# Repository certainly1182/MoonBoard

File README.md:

# MoonBoard - 75% ISO Keyboard with Hall Effect Sensors
This repository contains the hardware for a 75% ISO keyboard powered by hall effect sensors.<br />
[Click here for the firmware repository!](https://github.com/RephlexZero/qmk_firmware/tree/adc_testing)

## Features
- Hall Effect Sensors for configurable trigger point & "rapid trigger" functionality.
- Per-key RGB Lighting.
- USB connection uses [Unified Daughterboard](https://unified-daughterboard.github.io/).
- STM32 Microcontroller.
- Buzzer.
- 128x32 OLED Display.
- Rotary Encoder.
- Powered by QMK Firmware.

## Images

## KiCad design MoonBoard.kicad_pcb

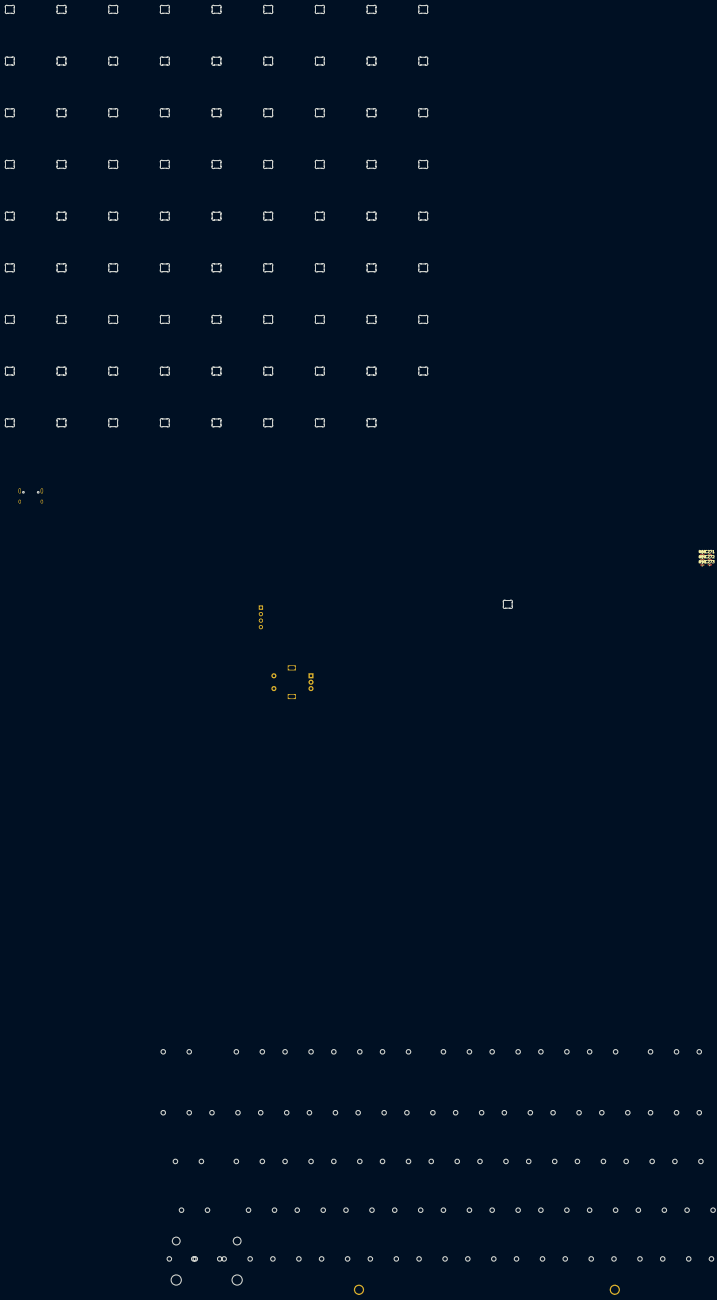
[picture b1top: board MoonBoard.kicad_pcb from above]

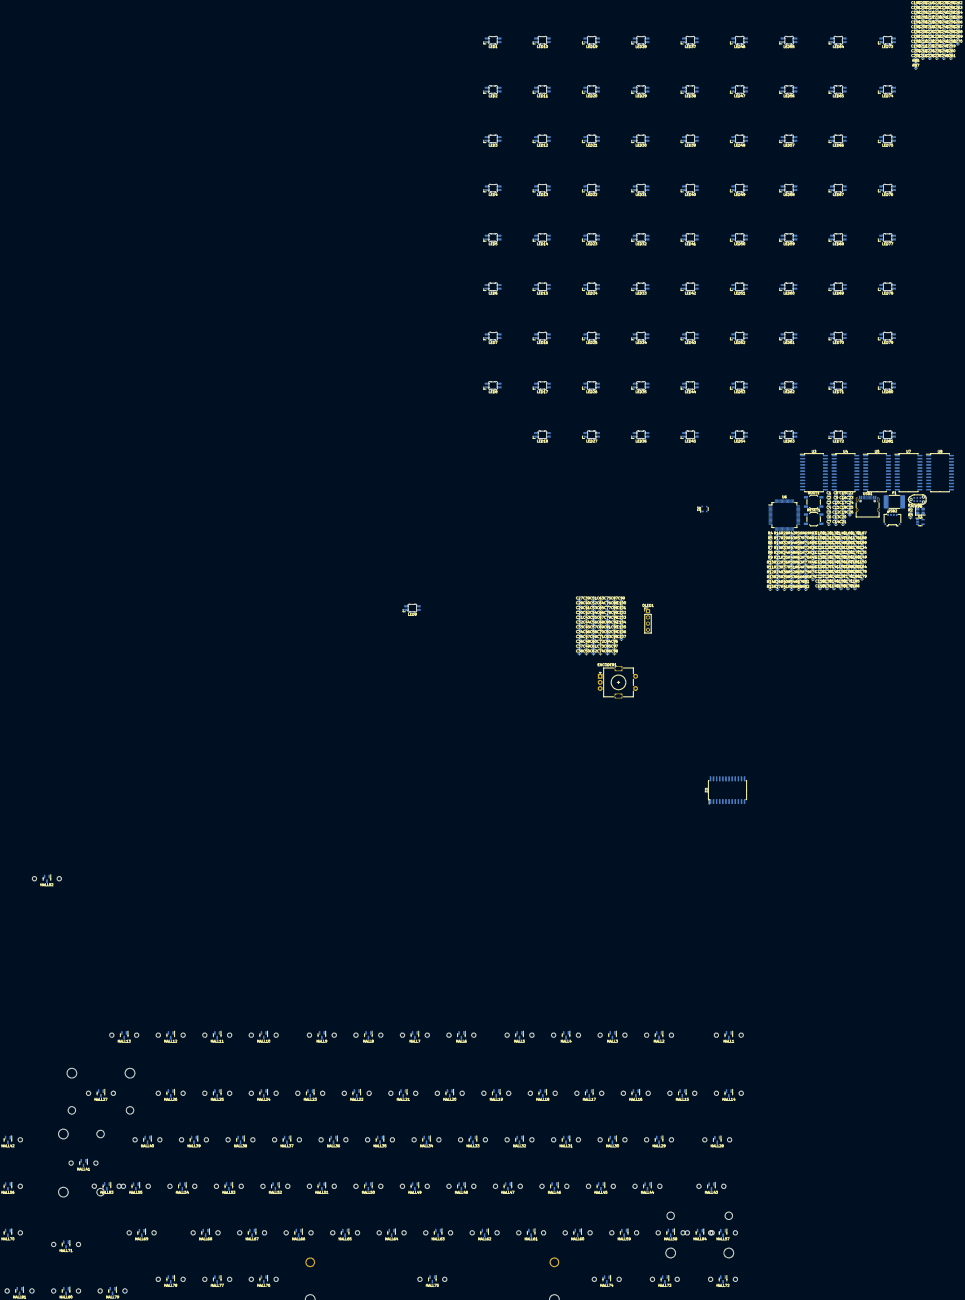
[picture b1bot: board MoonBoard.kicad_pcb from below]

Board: 2 copper layers, 551 parts (540 on the bottom side), 282 nets, no tracks yet.

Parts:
BOOT1: SW_SPST; SW_SPST_TL3342
C1, C2, C3, C4, C5, C6, C7, C12, C15, C16, C17, C18, C19, C20, C21, C22, C23, C24, C25, C26, C27, C28, C29, C30, C31, C32, C33, C34, C35, C36, C37, C38, C39, C40, C41, C42, C43, C44, C45, C46, C47, C48, C49, C50, C51, C52, C53, C54, C55, C56, C57, C58, C59, C60, C61, C62, C63, C64, C65, C66, C67, C68, C69, C70, C71, C72, C73, C74, C75, C76, C77, C78, C79, C80, C81, C82, C83, C84, C85, C86, C87, C88, C89, C90, C91, C92, C93, C94, C95, C96, C97, C98, C99, C100, C101, C102, C103, C104, C105, C106, C107, C108, C109, C110, C111, C112, C113, C114, C115, C116, C117, C118, C119, C120, C121, C122, C123, C124, C125, C126, C127, C128, C129, C130, C131, C132, C133, C134, C135, C136, C137, C138, C139, C140, C141, C142, C143, C144, C145, C146, C147, C148, C149, C150, C151, C152, C153, C154, C155, C156, C157, C158, C159, C160, C161, C162, C163, C164, C165, C166, C167, C168, C169, C170, C171, C172, C173, C174, C175, C176, C177, C178, C179, C180, C181, C182, C183, C184, C185, C186, C187, C188, C189, C190, C191, C192, C193, C194, C195, C196, C197, C198, C199, C200, C201, C202, C203, C204, C205, C206, C207, C208, C209, C210, C211, C212, C213, C214, C215, C216, C217, C218, C219, C220, C221, C222, C223, C224, C225, C226, C227, C228, C229, C230, C231, C232, C233, C234, C235, C236, C237, C238, C239, C240, C241, C242, C243, C244, C245, C246, C247, C248, C249, C250, C251, C252, C253, C254, C255, C256, C257, C258, C259, C260, C261, C262, C263, C264, C265, C266, C267, C268, C269, C270, C271, C272, C273: 100n; C_0402_1005Metric
C8, C9: 14p; C_0402_1005Metric
C10, C11: 2u2; C_0402_1005Metric
C13: 1u; C_0402_1005Metric
C14: 4u7; C_0402_1005Metric
D1: PRTR5V0U2X; SOT-143
ENCODER1: RotaryEncoder_Switch; RotaryEncoder_Alps_EC11E-Switch_Vertical_H20mm
F1: Fuse; Fuse_2920_7451Metric
HALL1, HALL2, HALL3, HALL4, HALL5, HALL6, HALL7, HALL8, HALL9, HALL10, HALL11, HALL12, HALL13, HALL14, HALL15, HALL16, HALL17, HALL18, HALL19, HALL20, HALL21, HALL22, HALL23, HALL24, HALL25, HALL26, HALL27, HALL29, HALL30, HALL31, HALL32, HALL33, HALL34, HALL35, HALL36, HALL37, HALL38, HALL39, HALL40, HALL41, HALL42, HALL44, HALL45, HALL46, HALL47, HALL48, HALL49, HALL50, HALL51, HALL52, HALL53, HALL54, HALL55, HALL56, HALL58, HALL59, HALL60, HALL61, HALL62, HALL63, HALL64, HALL65, HALL66, HALL67, HALL68, HALL70, HALL71, HALL75, HALL76, HALL77, HALL78, HALL79, HALL80, HALL81: SLSS49E-3; SLSS49E-3 with MX holes
HALL28, HALL82: SLSS49E-3; SLSS49E-3 with 1.5u MX holes
HALL43, HALL69: SLSS49E-3; SLSS49E-3 with 1.75u MX holes
HALL57, HALL72, HALL73, HALL74: SLSS49E-3; SLSS49E-3 with 1.25u MX holes
HALL83, HALL84: SLSS49E-3; SLSS49E-3 with 2.25 MX holes
LED1, LED2, LED3, LED4, LED5, LED6, LED7, LED8, LED9, LED10, LED11, LED12, LED13, LED14, LED15, LED16, LED17, LED18, LED19, LED20, LED21, LED22, LED23, LED24, LED25, LED26, LED27, LED28, LED29, LED30, LED31, LED32, LED33, LED34, LED35, LED36, LED37, LED38, LED39, LED40, LED41, LED42, LED43, LED44, LED45, LED46, LED47, LED48, LED49, LED50, LED51, LED52, LED53, LED54, LED55, LED56, LED57, LED58, LED59, LED60, LED61, LED62, LED63, LED64, LED65, LED66, LED67, LED68, LED69, LED70, LED71, LED72, LED73, LED74, LED75, LED76, LED77, LED78, LED79, LED80, LED81: MX_SK6812MINI-E; LED_MX_6028R
OLED1: Conn_01x04_Socket; PinHeader_1x04_P2.54mm_Vertical
R1, R2: 5k1; R_0402_1005Metric
R3, R4, R5, R6, R7, R8, R9, R10, R11, R12, R13, R14, R15, R16, R17, R18, R19, R20, R21, R22, R23, R24, R25, R26, R27, R28, R29, R30, R31, R32, R33, R34, R35, R36, R37, R38, R39, R40, R41, R42, R43, R44, R45, R46, R47, R48, R49, R50, R51, R52, R53, R54, R55, R56, R57, R58, R59, R60, R61, R62, R63, R64, R65, R66, R67, R68, R69, R70, R71, R72, R73, R74, R75, R76, R77, R78, R79, R80, R81, R82, R83, R84, R85, R88, R89, R90: 10k; R_0402_1005Metric
R86, R87: 470; R_0402_1005Metric
RESET1: SW_SPST; SW_SPST_TL3342
S27: STAB_MX_2u
S41: STAB_MX_ISO
S75: STAB_MX_P_6.25U; STAB_MX_P_6.25u
S83, S84: MX_stab; STAB_MX_2.25u
SWD1: TC2030_SWD; CON_TC2030_outlined
U1: AP2112K-3.3; SOT-23-5
U2, U3, U4, U5, U7, U8: CD74HC4067M; SOIC-24W_7.5x15.4mm_P1.27mm
U6: STM32F446RETx; LQFP-64_10x10mm_P0.5mm
USB1: USB_C_Receptacle_USB2.0; USB_C_Receptacle_HRO_TYPE-C-31-M-12
USB2: Conn_01x04_Socket; Molex_Pico-EZmate_78171-0004_1x04-1MP_P1.20mm_Vertical
Y1: 25MHz; Crystal_SMD_3225-4Pin_3.2x2.5mm

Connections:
+3V3: BOOT1.2 (B), C12.1, C13.1, C14.1, C15.1, C16.1, C17.1, C18.1, C19.1, C20.1, C21.1, C22.1, C23.1, C24.1, C25.1, C26.1, C27.1, C28.1, C29.1, C30.1, C31.1, C32.1, C33.1, C34.1, C35.1, C36.1, C37.1, C38.1, C39.1, C40.1, C41.1, C42.1, C43.1, C44.1, C45.1, C46.1, C47.1, C48.1, C49.1, C50.1, C51.1, C52.1, C53.1, C54.1, C55.1, C56.1, C57.1, C58.1, C59.1, C60.1, C61.1, C62.1, C63.1, C64.1, C65.1, C66.1, C67.1, C68.1, C69.1, C70.1, C71.1, C72.1, C73.1, C74.1, C75.1, C76.1, C77.1, C78.1, C79.1, C80.1, C81.1, C82.1, C83.1, C84.1, C85.1, C86.1, C87.1, C88.1, C89.1, C90.1, C91.1, C92.1, C93.1, C94.1, C95.1, C96.1, C97.1, C98.1, C99.1, C100.1, C101.1, C102.1, C103.1, C104.1, C105.1, C106.1, C107.1, ENCODER1.S1, HALL1.1 (VDD), HALL2.1 (VDD), HALL3.1 (VDD), HALL4.1 (VDD), HALL5.1 (VDD), HALL6.1 (VDD), HALL7.1 (VDD), HALL8.1 (VDD), HALL9.1 (VDD), HALL10.1 (VDD), HALL11.1 (VDD), HALL12.1 (VDD), HALL13.1 (VDD), HALL14.1 (VDD), HALL15.1 (VDD), HALL16.1 (VDD), HALL17.1 (VDD), HALL18.1 (VDD), HALL19.1 (VDD), HALL20.1 (VDD), HALL21.1 (VDD), HALL22.1 (VDD), HALL23.1 (VDD), HALL24.1 (VDD), HALL25.1 (VDD), HALL26.1 (VDD), HALL27.1 (VDD), HALL28.1 (VDD), HALL29.1 (VDD), HALL30.1 (VDD), HALL31.1 (VDD), HALL32.1 (VDD), HALL33.1 (VDD), HALL34.1 (VDD), HALL35.1 (VDD), HALL36.1 (VDD), HALL37.1 (VDD), HALL38.1 (VDD), HALL39.1 (VDD), HALL40.1 (VDD), HALL41.1 (VDD), HALL42.1 (VDD), HALL43.1 (VDD), HALL44.1 (VDD), HALL45.1 (VDD), HALL46.1 (VDD), HALL47.1 (VDD), HALL48.1 (VDD), HALL49.1 (VDD), HALL50.1 (VDD), HALL51.1 (VDD), HALL52.1 (VDD), HALL53.1 (VDD), HALL54.1 (VDD), HALL55.1 (VDD), HALL56.1 (VDD), HALL57.1 (VDD), HALL58.1 (VDD), HALL59.1 (VDD), HALL60.1 (VDD), HALL61.1 (VDD), HALL62.1 (VDD), HALL63.1 (VDD), HALL64.1 (VDD), HALL65.1 (VDD), HALL66.1 (VDD), HALL67.1 (VDD), HALL68.1 (VDD), HALL69.1 (VDD), HALL70.1 (VDD), HALL71.1 (VDD), HALL72.1 (VDD), HALL73.1 (VDD), HALL74.1 (VDD), HALL75.1 (VDD), HALL76.1 (VDD), HALL77.1 (VDD), HALL78.1 (VDD), HALL79.1 (VDD), HALL80.1 (VDD), HALL81.1 (VDD), HALL82.1 (VDD), HALL83.1 (VDD), HALL84.1 (VDD), SWD1.1 (VCC), U1.5 (VOUT), U6.1 (VBAT), U6.13 (VDDA), U6.19 (VDD), U6.32 (VDD), U6.48 (VDD), U6.64 (VDD)
+5V: C1.1, C2.1, C3.1, C4.1, C5.1, C6.1, C190.1, C191.1, C192.1, C193.1, C194.1, C195.1, C196.1, C197.1, C198.1, C199.1, C200.1, C201.1, C202.1, C203.1, C204.1, C205.1, C206.1, C207.1, C208.1, C209.1, C210.1, C211.1, C212.1, C213.1, C214.1, C215.1, C216.1, C217.1, C218.1, C219.1, C220.1, C221.1, C222.1, C223.1, C224.1, C225.1, C226.1, C227.1, C228.1, C229.1, C230.1, C231.1, C232.1, C233.1, C234.1, C235.1, C236.1, C237.1, C238.1, C239.1, C240.1, C241.1, C242.1, C243.1, C244.1, C245.1, C246.1, C247.1, C248.1, C249.1, C250.1, C251.1, C252.1, C253.1, C254.1, C255.1, C256.1, C257.1, C258.1, C259.1, C260.1, C261.1, C262.1, C263.1, C264.1, C265.1, C266.1, C267.1, C268.1, C269.1, C270.1, F1.2, LED1.1 (VDD), LED2.1 (VDD), LED3.1 (VDD), LED4.1 (VDD), LED5.1 (VDD), LED6.1 (VDD), LED7.1 (VDD), LED8.1 (VDD), LED9.1 (VDD), LED10.1 (VDD), LED11.1 (VDD), LED12.1 (VDD), LED13.1 (VDD), LED14.1 (VDD), LED15.1 (VDD), LED16.1 (VDD), LED17.1 (VDD), LED18.1 (VDD), LED19.1 (VDD), LED20.1 (VDD), LED21.1 (VDD), LED22.1 (VDD), LED23.1 (VDD), LED24.1 (VDD), LED25.1 (VDD), LED26.1 (VDD), LED27.1 (VDD), LED28.1 (VDD), LED29.1 (VDD), LED30.1 (VDD), LED31.1 (VDD), LED32.1 (VDD), LED33.1 (VDD), LED34.1 (VDD), LED35.1 (VDD), LED36.1 (VDD), LED37.1 (VDD), LED38.1 (VDD), LED39.1 (VDD), LED40.1 (VDD), LED41.1 (VDD), LED42.1 (VDD), LED43.1 (VDD), LED44.1 (VDD), LED45.1 (VDD), LED46.1 (VDD), LED47.1 (VDD), LED48.1 (VDD), LED49.1 (VDD), LED50.1 (VDD), LED51.1 (VDD), LED52.1 (VDD), LED53.1 (VDD), LED54.1 (VDD), LED55.1 (VDD), LED56.1 (VDD), LED57.1 (VDD), LED58.1 (VDD), LED59.1 (VDD), LED60.1 (VDD), LED61.1 (VDD), LED62.1 (VDD), LED63.1 (VDD), LED64.1 (VDD), LED65.1 (VDD), LED66.1 (VDD), LED67.1 (VDD), LED68.1 (VDD), LED69.1 (VDD), LED70.1 (VDD), LED71.1 (VDD), LED72.1 (VDD), LED73.1 (VDD), LED74.1 (VDD), LED75.1 (VDD), LED76.1 (VDD), LED77.1 (VDD), LED78.1 (VDD), LED79.1 (VDD), LED80.1 (VDD), LED81.1 (VDD), OLED1.3, U1.1 (VIN), U1.3 (EN), U2.24 (VCC), U3.24 (VCC), U4.24 (VCC), U5.24 (VCC), U7.24 (VCC), U8.24 (VCC), USB2.1
/BOOT0: BOOT1.1 (A), R3.1, U6.60 (BOOT0)
/VCAP_1: C10.1, C11.1, U6.30 (VCAP_1)
ADC123_IN0: U2.1 (COM), U6.14 (PA0)
ADC123_IN1: U3.1 (COM), U6.15 (PA1)
ADC123_IN2: U4.1 (COM), U6.16 (PA2)
ADC123_IN3: U5.1 (COM), U6.17 (PA3)
ADC123_IN10: U6.8 (PC0), U7.1 (COM)
ADC123_IN11: U6.9 (PC1), U8.1 (COM)
ENCODER_A: ENCODER1.A, U6.37 (PC6)
ENCODER_B: ENCODER1.B, U6.38 (PC7)
F_KEYS_0_0: R4.1, U2.9 (I0)
F_KEYS_0_1: R5.1, U2.8 (I1)
F_KEYS_0_2: R6.1, U2.7 (I2)
F_KEYS_0_3: R7.1, U2.6 (I3)
F_KEYS_0_4: R8.1, U2.5 (I4)
F_KEYS_0_5: R9.1, U2.4 (I5)
F_KEYS_0_6: R10.1, U2.3 (I6)
F_KEYS_0_7: R11.1, U2.2 (I7)
F_KEYS_0_8: R12.1, U2.23 (I8)
F_KEYS_0_9: R13.1, U2.22 (I9)
F_KEYS_0_10: R14.1, U2.21 (I10)
F_KEYS_0_11: R15.1, U2.20 (I11)
F_KEYS_0_12: R16.1, U2.19 (I12)
F_KEYS_1_0: R17.1, U3.9 (I0)
F_KEYS_1_1: R18.1, U3.8 (I1)
F_KEYS_1_2: R19.1, U3.7 (I2)
F_KEYS_1_3: R20.1, U3.6 (I3)
F_KEYS_1_4: R21.1, U3.5 (I4)
F_KEYS_1_5: R22.1, U3.4 (I5)
F_KEYS_1_6: R23.1, U3.3 (I6)
F_KEYS_1_7: R24.1, U3.2 (I7)
F_KEYS_1_8: R25.1, U3.23 (I8)
F_KEYS_1_9: R26.1, U3.22 (I9)
F_KEYS_1_10: R27.1, U3.21 (I10)
F_KEYS_1_11: R28.1, U3.20 (I11)
F_KEYS_1_12: R29.1, U3.19 (I12)
F_KEYS_1_13: R30.1, U3.18 (I13)
F_KEYS_1_14: R31.1, U3.17 (I14)
F_KEYS_2_0: R32.1, U4.9 (I0)
F_KEYS_2_1: R33.1, U4.8 (I1)
F_KEYS_2_2: R34.1, U4.7 (I2)
F_KEYS_2_3: R35.1, U4.6 (I3)
F_KEYS_2_4: R36.1, U4.5 (I4)
F_KEYS_2_5: R37.1, U4.4 (I5)
F_KEYS_2_6: R38.1, U4.3 (I6)
F_KEYS_2_7: R39.1, U4.2 (I7)
F_KEYS_2_8: R40.1, U4.23 (I8)
F_KEYS_2_9: R41.1, U4.22 (I9)
F_KEYS_2_10: R42.1, U4.21 (I10)
F_KEYS_2_11: R43.1, U4.20 (I11)
F_KEYS_2_12: R44.1, U4.19 (I12)
F_KEYS_2_13: R45.1, U4.18 (I13)
F_KEYS_2_14: R46.1, U4.17 (I14)
F_KEYS_3_0: R47.1, U5.9 (I0)
F_KEYS_3_1: R48.1, U5.8 (I1)
F_KEYS_3_2: R49.1, U5.7 (I2)
F_KEYS_3_3: R50.1, U5.6 (I3)
F_KEYS_3_4: R51.1, U5.5 (I4)
F_KEYS_3_5: R52.1, U5.4 (I5)
F_KEYS_3_6: R53.1, U5.3 (I6)
F_KEYS_3_7: R54.1, U5.2 (I7)
F_KEYS_3_8: R55.1, U5.23 (I8)
F_KEYS_3_9: R56.1, U5.22 (I9)
F_KEYS_3_10: R57.1, U5.21 (I10)
F_KEYS_3_11: R58.1, U5.20 (I11)
F_KEYS_3_12: R59.1, U5.19 (I12)
F_KEYS_3_13: R60.1, U5.18 (I13)
F_KEYS_3_14: R89.1, U5.17 (I14)
F_KEYS_4_0: R61.1, U7.9 (I0)
F_KEYS_4_1: R62.1, U7.8 (I1)
F_KEYS_4_2: R63.1, U7.7 (I2)
F_KEYS_4_3: R64.1, U7.6 (I3)
F_KEYS_4_4: R65.1, U7.5 (I4)
F_KEYS_4_5: R66.1, U7.4 (I5)
F_KEYS_4_6: R67.1, U7.3 (I6)
F_KEYS_4_7: R68.1, U7.2 (I7)
F_KEYS_4_8: R69.1, U7.23 (I8)
F_KEYS_4_9: R70.1, U7.22 (I9)
F_KEYS_4_10: R71.1, U7.21 (I10)
F_KEYS_4_11: R72.1, U7.20 (I11)
F_KEYS_4_12: R73.1, U7.19 (I12)
F_KEYS_4_13: R74.1, U7.18 (I13)
F_KEYS_4_14: R75.1, U7.17 (I14)
F_KEYS_4_15: R90.1, U7.16 (I15)
F_KEYS_5_0: R76.1, U8.9 (I0)
F_KEYS_5_1: R77.1, U8.8 (I1)
F_KEYS_5_2: R78.1, U8.7 (I2)
F_KEYS_5_3: R79.1, U8.6 (I3)
F_KEYS_5_4: R80.1, U8.5 (I4)
F_KEYS_5_5: R81.1, U8.4 (I5)
F_KEYS_5_6: R82.1, U8.3 (I6)
F_KEYS_5_7: R83.1, U8.2 (I7)
F_KEYS_5_8: R84.1, U8.23 (I8)
F_KEYS_5_9: R85.1, U8.22 (I9)
GND: C1.2, C2.2, C3.2, C4.2, C5.2, C6.2, C7.2, C8.2, C9.2, C10.2, C11.2, C12.2, C13.2, C14.2, C15.2, C16.2, C17.2, C18.2, C19.2, C20.2, C21.2, C22.2, C23.2, C24.2, C25.2, C26.2, C27.2, C28.2, C29.2, C30.2, C31.2, C32.2, C33.2, C34.2, C35.2, C36.2, C37.2, C38.2, C39.2, C40.2, C41.2, C42.2, C43.2, C44.2, C45.2, C46.2, C47.2, C48.2, C49.2, C50.2, C51.2, C52.2, C53.2, C54.2, C55.2, C56.2, C57.2, C58.2, C59.2, C60.2, C61.2, C62.2, C63.2, C64.2, C65.2, C66.2, C67.2, C68.2, C69.2, C70.2, C71.2, C72.2, C73.2, C74.2, C75.2, C76.2, C77.2, C78.2, C79.2, C80.2, C81.2, C82.2, C83.2, C84.2, C85.2, C86.2, C87.2, C88.2, C89.2, C90.2, C91.2, C92.2, C93.2, C94.2, C95.2, C96.2, C97.2, C98.2, C99.2, C100.2, C101.2, C102.2, C103.2, C104.2, C105.2, C106.2, C107.2, C108.2, C109.2, C110.2, C111.2, C112.2, C113.2, C114.2, C115.2, C116.2, C117.2, C118.2, C119.2, C120.2, C121.2, C122.2, C123.2, C124.2, C125.2, C126.2, C127.2, C128.2, C129.2, C130.2, C131.2, C132.2, C133.2, C134.2, C135.2, C136.2, C137.2, C138.2, C139.2, C140.2, C141.2, C142.2, C143.2, C144.2, C145.2, C146.2, C147.2, C148.2, C149.2, C150.2, C151.2, C152.2, C153.2, C154.2, C155.2, C156.2, C157.2, C158.2, C159.2, C160.2, C161.2, C162.2, C163.2, C164.2, C165.2, C166.2, C167.2, C168.2, C169.2, C170.2, C171.2, C172.2, C173.2, C174.2, C175.2, C176.2, C177.2, C178.2, C179.2, C180.2, C181.2, C182.2, C183.2, C184.2, C185.2, C186.2, C187.2, C188.2, C189.2, C190.2, C191.2, C192.2, C193.2, C194.2, C195.2, C196.2, C197.2, C198.2, C199.2, C200.2, C201.2, C202.2, C203.2, C204.2, C205.2, C206.2, C207.2, C208.2, C209.2, C210.2, C211.2, C212.2, C213.2, C214.2, C215.2, C216.2, C217.2, C218.2, C219.2, C220.2, C221.2, C222.2, C223.2, C224.2, C225.2, C226.2, C227.2, C228.2, C229.2, C230.2, C231.2, C232.2, C233.2, C234.2, C235.2, C236.2, C237.2, C238.2, C239.2, C240.2, C241.2, C242.2, C243.2, C244.2, C245.2, C246.2, C247.2, C248.2, C249.2, C250.2, C251.2, C252.2, C253.2, C254.2, C255.2, C256.2, C257.2, C258.2, C259.2, C260.2, C261.2, C262.2, C263.2, C264.2, C265.2, C266.2, C267.2, C268.2, C269.2, C270.2, C271.2, C272.2, C273.2, D1.1 (GND), ENCODER1.C, HALL1.2 (GND), HALL2.2 (GND), HALL3.2 (GND), HALL4.2 (GND), HALL5.2 (GND), HALL6.2 (GND), HALL7.2 (GND), HALL8.2 (GND), HALL9.2 (GND), HALL10.2 (GND), HALL11.2 (GND), HALL12.2 (GND), HALL13.2 (GND), HALL14.2 (GND), HALL15.2 (GND), HALL16.2 (GND), HALL17.2 (GND), HALL18.2 (GND), HALL19.2 (GND), HALL20.2 (GND), HALL21.2 (GND), HALL22.2 (GND), HALL23.2 (GND), HALL24.2 (GND), HALL25.2 (GND), HALL26.2 (GND), HALL27.2 (GND), HALL28.2 (GND), HALL29.2 (GND), HALL30.2 (GND), HALL31.2 (GND), HALL32.2 (GND), HALL33.2 (GND), HALL34.2 (GND), HALL35.2 (GND), HALL36.2 (GND), HALL37.2 (GND), HALL38.2 (GND), HALL39.2 (GND), HALL40.2 (GND), HALL41.2 (GND), HALL42.2 (GND), HALL43.2 (GND), HALL44.2 (GND), HALL45.2 (GND), HALL46.2 (GND), HALL47.2 (GND), HALL48.2 (GND), HALL49.2 (GND), HALL50.2 (GND), HALL51.2 (GND), HALL52.2 (GND), HALL53.2 (GND), HALL54.2 (GND), HALL55.2 (GND), HALL56.2 (GND), HALL57.2 (GND), HALL58.2 (GND), HALL59.2 (GND), HALL60.2 (GND), HALL61.2 (GND), HALL62.2 (GND), HALL63.2 (GND), HALL64.2 (GND), HALL65.2 (GND), HALL66.2 (GND), HALL67.2 (GND), HALL68.2 (GND), HALL69.2 (GND), HALL70.2 (GND), HALL71.2 (GND), HALL72.2 (GND), HALL73.2 (GND), HALL74.2 (GND), HALL75.2 (GND), HALL76.2 (GND), HALL77.2 (GND), HALL78.2 (GND), HALL79.2 (GND), HALL80.2 (GND), HALL81.2 (GND), HALL82.2 (GND), HALL83.2 (GND), HALL84.2 (GND), LED1.4 (VSS), LED2.4 (VSS), LED3.4 (VSS), LED4.4 (VSS), LED5.4 (VSS), LED6.4 (VSS), LED7.4 (VSS), LED8.4 (VSS), LED9.4 (VSS), LED10.4 (VSS), LED11.4 (VSS), LED12.4 (VSS), LED13.4 (VSS), LED14.4 (VSS), LED15.4 (VSS), LED16.4 (VSS), LED17.4 (VSS), LED18.4 (VSS), LED19.4 (VSS), LED20.4 (VSS), LED21.4 (VSS), LED22.4 (VSS), LED23.4 (VSS), LED24.4 (VSS), LED25.4 (VSS), LED26.4 (VSS), LED27.4 (VSS), LED28.4 (VSS), LED29.4 (VSS), LED30.4 (VSS), LED31.4 (VSS), LED32.4 (VSS), LED33.4 (VSS), LED34.4 (VSS), LED35.4 (VSS), LED36.4 (VSS), LED37.4 (VSS), LED38.4 (VSS), LED39.4 (VSS), LED40.4 (VSS), LED41.4 (VSS), LED42.4 (VSS), LED43.4 (VSS), LED44.4 (VSS), LED45.4 (VSS), LED46.4 (VSS), LED47.4 (VSS), LED48.4 (VSS), LED49.4 (VSS), LED50.4 (VSS), LED51.4 (VSS), LED52.4 (VSS), LED53.4 (VSS), LED54.4 (VSS), LED55.4 (VSS), LED56.4 (VSS), LED57.4 (VSS), LED58.4 (VSS), LED59.4 (VSS), LED60.4 (VSS), LED61.4 (VSS), LED62.4 (VSS), LED63.4 (VSS), LED64.4 (VSS), LED65.4 (VSS), LED66.4 (VSS), LED67.4 (VSS), LED68.4 (VSS), LED69.4 (VSS), LED70.4 (VSS), LED71.4 (VSS), LED72.4 (VSS), LED73.4 (VSS), LED74.4 (VSS), LED75.4 (VSS), LED76.4 (VSS), LED77.4 (VSS), LED78.4 (VSS), LED79.4 (VSS), LED80.4 (VSS), LED81.4 (VSS), OLED1.4, R1.2, R2.2, R3.2, R87.2, RESET1.1 (A), SWD1.5 (GND), U1.2 (GND), U2.12 (GND), U2.15 (~E), U3.12 (GND), U3.15 (~E), U4.12 (GND), U4.15 (~E), U5.12 (GND), U5.15 (~E), U6.12 (VSSA), U6.18 (VSS), U6.31 (VSS), U6.47 (VSS), U6.63 (VSS), U7.12 (GND), U7.15 (~E), U8.12 (GND), U8.15 (~E), USB1.A1 (GND), USB1.A12 (GND), USB1.B1 (GND), USB1.B12 (GND), USB2.4, Y1.2, Y1.4
I2C1_SCL: OLED1.2, U6.58 (PB6)
I2C1_SDA: OLED1.1, U6.59 (PB7)
KEYS_0_0: C108.1, HALL1.3 (VOUT), R4.2
KEYS_0_1: C109.1, HALL2.3 (VOUT), R5.2
KEYS_0_2: C110.1, HALL3.3 (VOUT), R6.2
KEYS_0_3: C111.1, HALL4.3 (VOUT), R7.2
KEYS_0_4: C112.1, HALL5.3 (VOUT), R8.2
KEYS_0_5: C113.1, HALL6.3 (VOUT), R9.2
KEYS_0_6: C114.1, HALL7.3 (VOUT), R10.2
KEYS_0_7: C115.1, HALL8.3 (VOUT), R11.2
KEYS_0_8: C116.1, HALL9.3 (VOUT), R12.2
KEYS_0_9: C117.1, HALL10.3 (VOUT), R13.2
KEYS_0_10: C118.1, HALL11.3 (VOUT), R14.2
KEYS_0_11: C119.1, HALL12.3 (VOUT), R15.2
KEYS_0_12: C120.1, HALL13.3 (VOUT), R16.2
KEYS_1_0: C121.1, HALL14.3 (VOUT), R17.2
KEYS_1_1: C122.1, HALL15.3 (VOUT), R18.2
KEYS_1_2: C123.1, HALL16.3 (VOUT), R19.2
KEYS_1_3: C124.1, HALL17.3 (VOUT), R20.2
KEYS_1_4: C125.1, HALL18.3 (VOUT), R21.2
KEYS_1_5: C126.1, HALL19.3 (VOUT), R22.2
KEYS_1_6: C127.1, HALL20.3 (VOUT), R23.2
KEYS_1_7: C128.1, HALL21.3 (VOUT), R24.2
KEYS_1_8: C129.1, HALL22.3 (VOUT), R25.2
KEYS_1_9: C130.1, HALL23.3 (VOUT), R26.2
KEYS_1_10: C131.1, HALL24.3 (VOUT), R27.2
KEYS_1_11: C132.1, HALL25.3 (VOUT), R28.2
KEYS_1_12: C133.1, HALL26.3 (VOUT), R29.2
KEYS_1_13: C134.1, HALL27.3 (VOUT), R30.2
KEYS_1_14: C135.1, ENCODER1.S2, R31.2
KEYS_2_0: C136.1, HALL28.3 (VOUT), R32.2
KEYS_2_1: C137.1, HALL29.3 (VOUT), R33.2
KEYS_2_2: C138.1, HALL30.3 (VOUT), R34.2
KEYS_2_3: C139.1, HALL31.3 (VOUT), R35.2
KEYS_2_4: C140.1, HALL32.3 (VOUT), R36.2
KEYS_2_5: C141.1, HALL33.3 (VOUT), R37.2
KEYS_2_6: C142.1, HALL34.3 (VOUT), R38.2
KEYS_2_7: C143.1, HALL35.3 (VOUT), R39.2
KEYS_2_8: C144.1, HALL36.3 (VOUT), R40.2
KEYS_2_9: C145.1, HALL37.3 (VOUT), R41.2
KEYS_2_10: C146.1, HALL38.3 (VOUT), R42.2
KEYS_2_11: C147.1, HALL39.3 (VOUT), R43.2
KEYS_2_12: C148.1, HALL40.3 (VOUT), R44.2
KEYS_2_13: C149.1, HALL41.3 (VOUT), R45.2
KEYS_2_14: C150.1, HALL42.3 (VOUT), R46.2
KEYS_2_15: C271.1, HALL82.3 (VOUT), R88.2
KEYS_3_0: C151.1, HALL43.3 (VOUT), R47.2
KEYS_3_1: C152.1, HALL44.3 (VOUT), R48.2
KEYS_3_2: C153.1, HALL45.3 (VOUT), R49.2
KEYS_3_3: C154.1, HALL46.3 (VOUT), R50.2
KEYS_3_4: C155.1, HALL47.3 (VOUT), R51.2
KEYS_3_5: C156.1, HALL48.3 (VOUT), R52.2
KEYS_3_6: C157.1, HALL49.3 (VOUT), R53.2
KEYS_3_7: C158.1, HALL50.3 (VOUT), R54.2
KEYS_3_8: C159.1, HALL51.3 (VOUT), R55.2
KEYS_3_9: C160.1, HALL52.3 (VOUT), R56.2
KEYS_3_10: C161.1, HALL53.3 (VOUT), R57.2
KEYS_3_11: C162.1, HALL54.3 (VOUT), R58.2
KEYS_3_12: C163.1, HALL55.3 (VOUT), R59.2
KEYS_3_13: C164.1, HALL56.3 (VOUT), R60.2
KEYS_3_14: C272.1, HALL83.3 (VOUT), R89.2
KEYS_4_0: C165.1, HALL57.3 (VOUT), R61.2
KEYS_4_1: C166.1, HALL58.3 (VOUT), R62.2
KEYS_4_2: C167.1, HALL59.3 (VOUT), R63.2
KEYS_4_3: C168.1, HALL60.3 (VOUT), R64.2
KEYS_4_4: C169.1, HALL61.3 (VOUT), R65.2
KEYS_4_5: C170.1, HALL62.3 (VOUT), R66.2
KEYS_4_6: C171.1, HALL63.3 (VOUT), R67.2
KEYS_4_7: C172.1, HALL64.3 (VOUT), R68.2
KEYS_4_8: C173.1, HALL65.3 (VOUT), R69.2
KEYS_4_9: C174.1, HALL66.3 (VOUT), R70.2
KEYS_4_10: C175.1, HALL67.3 (VOUT), R71.2
KEYS_4_11: C176.1, HALL68.3 (VOUT), R72.2
KEYS_4_12: C177.1, HALL69.3 (VOUT), R73.2
KEYS_4_13: C178.1, HALL71.3 (VOUT), R74.2
KEYS_4_14: C179.1, HALL70.3 (VOUT), R75.2
KEYS_4_15: C273.1, HALL84.3 (VOUT), R90.2
KEYS_5_0: C180.1, HALL72.3 (VOUT), R76.2
KEYS_5_1: C181.1, HALL73.3 (VOUT), R77.2
KEYS_5_2: C182.1, HALL74.3 (VOUT), R78.2
KEYS_5_3: C183.1, HALL75.3 (VOUT), R79.2
KEYS_5_4: C184.1, HALL76.3 (VOUT), R80.2
KEYS_5_5: C185.1, HALL77.3 (VOUT), R81.2
KEYS_5_6: C186.1, HALL78.3 (VOUT), R82.2
KEYS_5_7: C187.1, HALL79.3 (VOUT), R83.2
KEYS_5_8: C188.1, HALL80.3 (VOUT), R84.2
KEYS_5_9: C189.1, HALL81.3 (VOUT), R85.2
NRESET: C7.1, RESET1.2 (B), SWD1.3 (~RST), U6.7 (NRST)
unnamed: LED1.3 (DIN), R86.2
unnamed: LED1.2 (DOUT), LED2.3 (DIN)
unnamed: LED2.2 (DOUT), LED3.3 (DIN)
unnamed: LED3.2 (DOUT), LED4.3 (DIN)
unnamed: LED4.2 (DOUT), LED5.3 (DIN)
unnamed: LED5.2 (DOUT), LED6.3 (DIN)
unnamed: LED6.2 (DOUT), LED7.3 (DIN)
unnamed: LED7.2 (DOUT), LED8.3 (DIN)
unnamed: LED8.2 (DOUT), LED9.3 (DIN)
unnamed: LED9.2 (DOUT), LED10.3 (DIN)
unnamed: LED10.2 (DOUT), LED11.3 (DIN)
unnamed: LED11.2 (DOUT), LED12.3 (DIN)
unnamed: LED12.2 (DOUT), LED13.3 (DIN)
unnamed: LED13.2 (DOUT), LED14.3 (DIN)
unnamed: LED14.2 (DOUT), LED15.3 (DIN)
unnamed: LED15.2 (DOUT), LED16.3 (DIN)
unnamed: LED16.2 (DOUT), LED17.3 (DIN)
unnamed: LED17.2 (DOUT), LED18.3 (DIN)
unnamed: LED18.2 (DOUT), LED19.3 (DIN)
unnamed: LED19.2 (DOUT), LED20.3 (DIN)
unnamed: LED20.2 (DOUT), LED21.3 (DIN)
unnamed: LED21.2 (DOUT), LED22.3 (DIN)
unnamed: LED22.2 (DOUT), LED23.3 (DIN)
unnamed: LED23.2 (DOUT), LED24.3 (DIN)
unnamed: LED24.2 (DOUT), LED25.3 (DIN)
unnamed: LED25.2 (DOUT), LED26.3 (DIN)
unnamed: LED26.2 (DOUT), LED27.3 (DIN)
unnamed: LED27.2 (DOUT), LED28.3 (DIN)
unnamed: LED28.2 (DOUT), LED29.3 (DIN)
unnamed: LED29.2 (DOUT), LED30.3 (DIN)
unnamed: LED30.2 (DOUT), LED31.3 (DIN)
unnamed: LED31.2 (DOUT), LED32.3 (DIN)
unnamed: LED32.2 (DOUT), LED33.3 (DIN)
unnamed: LED33.2 (DOUT), LED34.3 (DIN)
unnamed: LED34.2 (DOUT), LED35.3 (DIN)
unnamed: LED35.2 (DOUT), LED36.3 (DIN)
unnamed: LED36.2 (DOUT), LED37.3 (DIN)
unnamed: LED37.2 (DOUT), LED38.3 (DIN)
unnamed: LED38.2 (DOUT), LED39.3 (DIN)
unnamed: LED39.2 (DOUT), LED40.3 (DIN)
unnamed: LED40.2 (DOUT), LED41.3 (DIN)
unnamed: LED41.2 (DOUT), LED42.3 (DIN)
unnamed: LED42.2 (DOUT), LED43.3 (DIN)
unnamed: LED43.2 (DOUT), LED44.3 (DIN)
unnamed: LED44.2 (DOUT), LED45.3 (DIN)
unnamed: LED45.2 (DOUT), LED46.3 (DIN)
unnamed: LED46.2 (DOUT), LED47.3 (DIN)
unnamed: LED47.2 (DOUT), LED48.3 (DIN)
unnamed: LED48.2 (DOUT), LED49.3 (DIN)
unnamed: LED49.2 (DOUT), LED50.3 (DIN)
unnamed: LED50.2 (DOUT), LED51.3 (DIN)
unnamed: LED51.2 (DOUT), LED52.3 (DIN)
unnamed: LED52.2 (DOUT), LED53.3 (DIN)
unnamed: LED53.2 (DOUT), LED54.3 (DIN)
unnamed: LED54.2 (DOUT), LED55.3 (DIN)
unnamed: LED55.2 (DOUT), LED56.3 (DIN)
unnamed: LED56.2 (DOUT), LED57.3 (DIN)
unnamed: LED57.2 (DOUT), LED58.3 (DIN)
unnamed: LED58.2 (DOUT), LED59.3 (DIN)
unnamed: LED59.2 (DOUT), LED60.3 (DIN)
unnamed: LED60.2 (DOUT), LED61.3 (DIN)
unnamed: LED61.2 (DOUT), LED62.3 (DIN)
unnamed: LED62.2 (DOUT), LED63.3 (DIN)
unnamed: LED63.2 (DOUT), LED64.3 (DIN)
unnamed: LED64.2 (DOUT), LED65.3 (DIN)
unnamed: LED65.2 (DOUT), LED66.3 (DIN)
unnamed: LED66.2 (DOUT), LED67.3 (DIN)
unnamed: LED67.2 (DOUT), LED68.3 (DIN)
unnamed: LED68.2 (DOUT), LED69.3 (DIN)
unnamed: LED69.2 (DOUT), LED70.3 (DIN)
unnamed: LED70.2 (DOUT), LED71.3 (DIN)
unnamed: LED71.2 (DOUT), LED72.3 (DIN)
unnamed: LED72.2 (DOUT), LED73.3 (DIN)
unnamed: LED73.2 (DOUT), LED74.3 (DIN)
unnamed: LED74.2 (DOUT), LED75.3 (DIN)
unnamed: LED75.2 (DOUT), LED76.3 (DIN)
unnamed: LED76.2 (DOUT), LED77.3 (DIN)
unnamed: LED77.2 (DOUT), LED78.3 (DIN)
unnamed: LED78.2 (DOUT), LED79.3 (DIN)
unnamed: LED79.2 (DOUT), LED80.3 (DIN)
unnamed: LED80.2 (DOUT), LED81.3 (DIN)
unnamed: LED81.2 (DOUT), R87.1
unnamed: R1.1, USB1.A5 (CC1)
unnamed: R2.1, USB1.B5 (CC2)
OSC_IN: C8.1, U6.5 (PH0), Y1.1
OSC_OUT: C9.1, U6.6 (PH1), Y1.3
RGB_DIN: R86.1, U6.25 (PC5)
S0: U2.10 (S0), U3.10 (S0), U4.10 (S0), U5.10 (S0), U6.20 (PA4), U7.10 (S0), U8.10 (S0)
S1: U2.11 (S1), U3.11 (S1), U4.11 (S1), U5.11 (S1), U6.21 (PA5), U7.11 (S1), U8.11 (S1)
S2: U2.14 (S2), U3.14 (S2), U4.14 (S2), U5.14 (S2), U6.22 (PA6), U7.14 (S2), U8.14 (S2)
S3: U2.13 (S3), U3.13 (S3), U4.13 (S3), U5.13 (S3), U6.23 (PA7), U7.13 (S3), U8.13 (S3)
SWCLK: SWD1.4 (SWCLK), U6.49 (PA14)
SWDIO: SWD1.2 (SWDIO), U6.46 (PA13)
SWO: SWD1.6 (SWO), U6.55 (PB3)
USB_D+: D1.2 (I/O1), U6.45 (PA12), USB1.A6 (D+), USB1.B6 (D+), USB2.3
USB_D-: D1.3 (I/O2), U6.44 (PA11), USB1.A7 (D-), USB1.B7 (D-), USB2.2
VBUS: D1.4 (VCC), F1.1, USB1.A4 (VBUS), USB1.A9 (VBUS), USB1.B4 (VBUS), USB1.B9 (VBUS)

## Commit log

2023-07-29 second commit
2023-07-30 assign footprints
2023-07-31 switch layout
2023-07-31 final key layout
2023-08-02 key filter
2023-08-05 key filters
2023-08-06 switch power routed
2023-08-09 Create LICENSE
2023-08-09 rearrange LEDs
2023-08-09 license and readme
2023-08-10 redo edge cuts
2023-08-10 remove superfluous usb connector
2023-08-15 add lcsc part no.s
2023-08-15 change some pins
2023-08-17 restructure schematic to use hierarchical sheets
2023-08-18 fix sheet numbering
2023-08-19 fix most broken traces
2023-08-20 finish most routing
2023-08-22 layout rgb using sheets
2023-08-24 move mux1
2023-08-24 fix thermal relief
2023-08-24 usb hub awfulness
2023-08-26 make room for usb connectors
2023-09-03 finish routing
2023-09-04 add silkscreen, led models
2023-09-14 switch to SOIC multiplexers
2023-09-24 add level shifter for rgb data line
2023-09-24 fillet corners
2023-09-27 fix LED footprint, add boot/reset jumpers
2023-09-29 add speculative mounting holes
2023-10-10 add reverse polarity protection to LDO
2023-11-02 buzz
2023-11-03 f303
2023-11-03 change HSE
2023-11-04 f303 routing
2023-11-04 dip switch
2023-11-05 tidy up
2023-11-05 tvs & less fun
2023-11-20 add usb D+ pullup
2023-12-03 timer encoder mode
2023-12-20 make VDDA ~2V
2024-01-13 new board outline remove VBUS PI filter
2024-01-24 add 0R usb termination resistors change muxes to 3V3
2024-02-18 update holes
2024-02-18 remove bad level shifter
2024-02-23 enlarge rgb pads
2024-05-07 tidy up readme
2024-05-07 fix readme
2024-05-07 update to kicad 8
2024-05-07 fix image render v2
2024-05-07 fix image render v3
2024-05-07 fix readme image
2024-05-07 fix yaml spacing
2024-05-07 readme image fix attempt 2
2024-05-07 fix sk6812-rot hole
2024-10-14 Update README.md with link to firmware
